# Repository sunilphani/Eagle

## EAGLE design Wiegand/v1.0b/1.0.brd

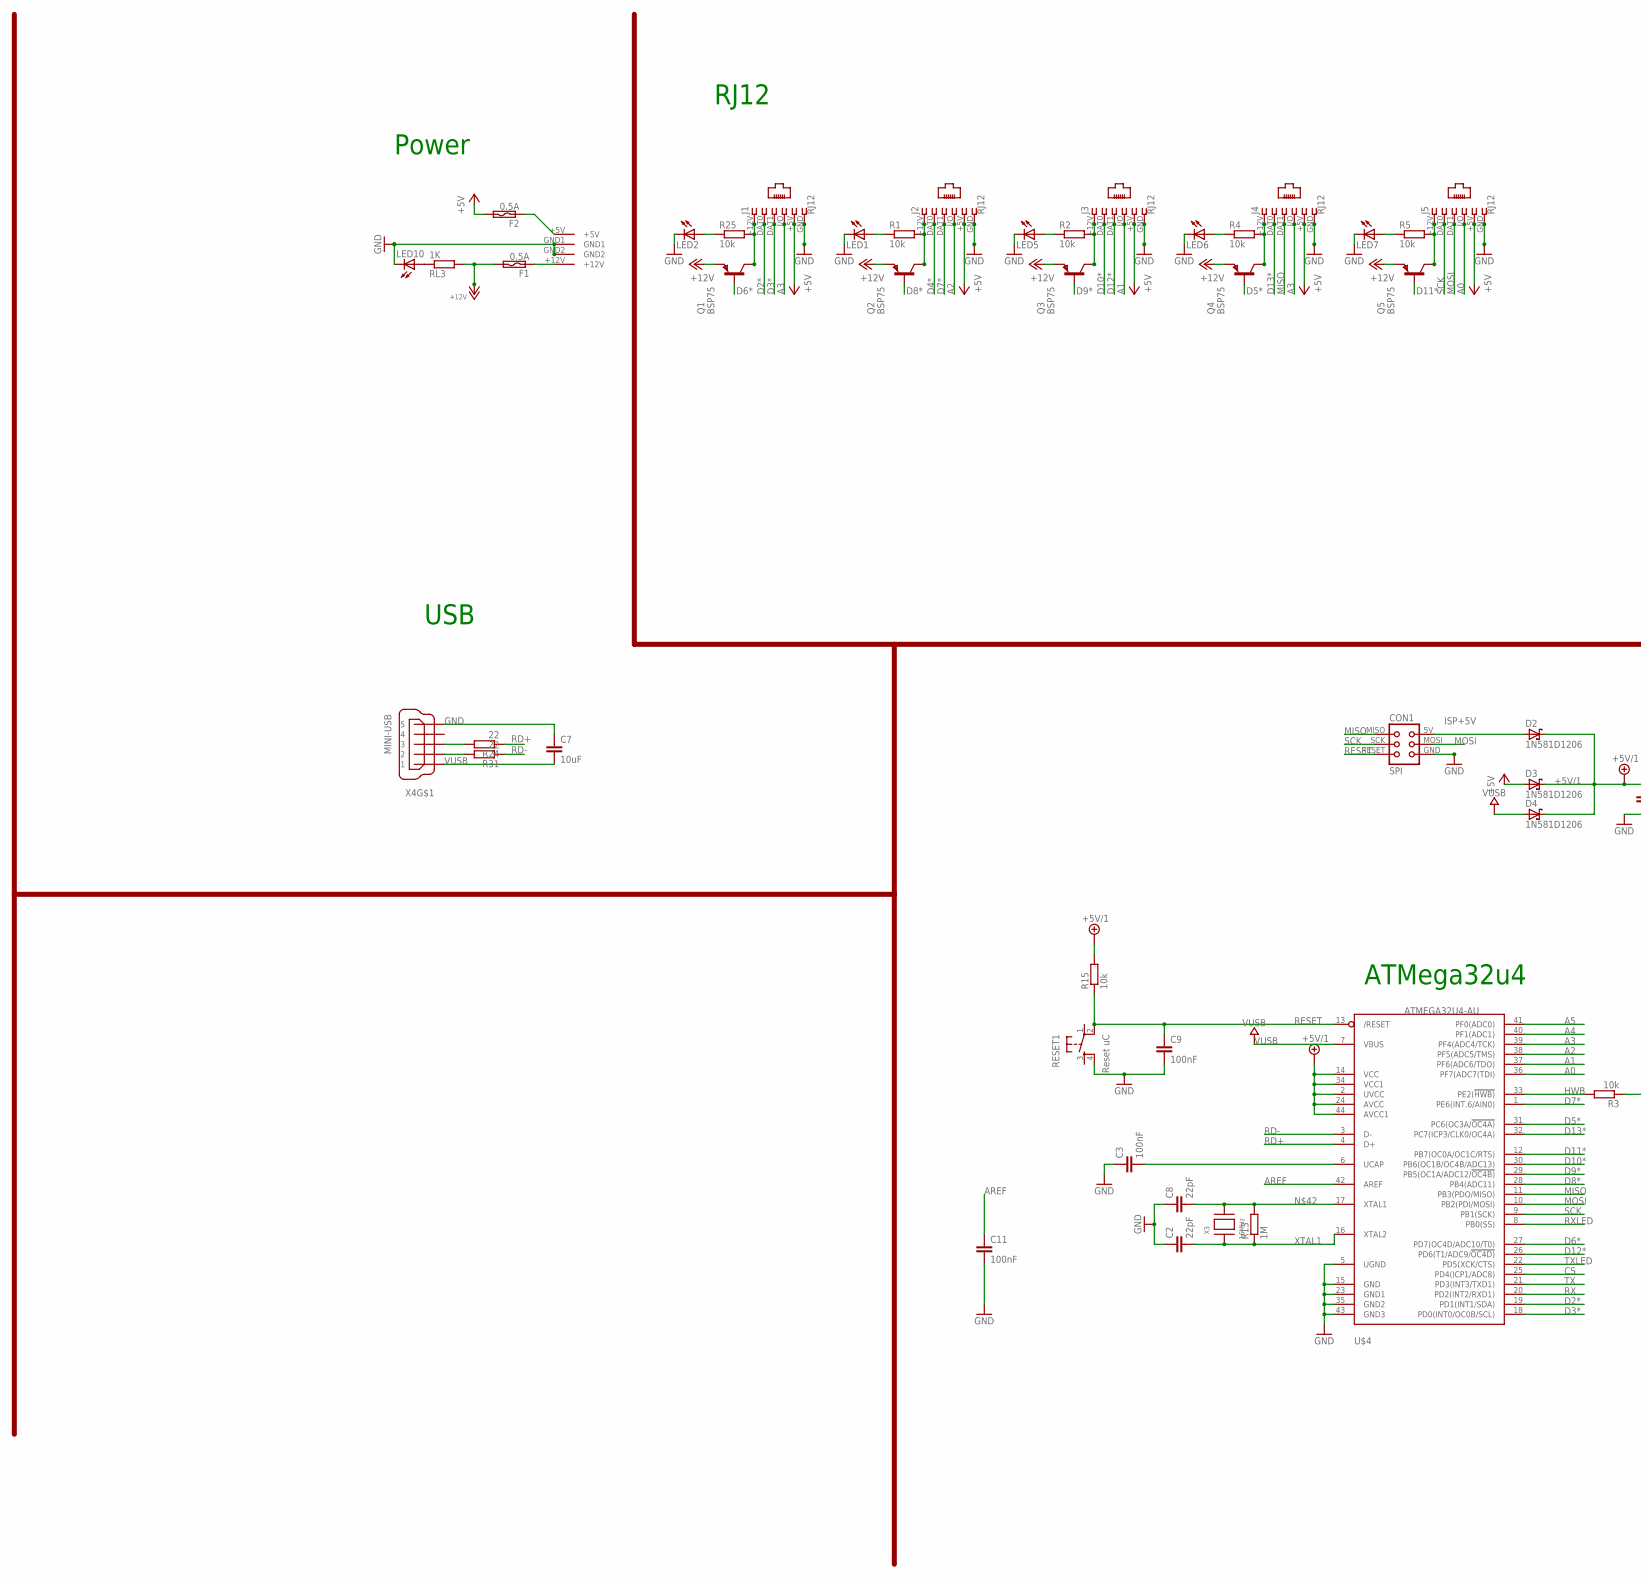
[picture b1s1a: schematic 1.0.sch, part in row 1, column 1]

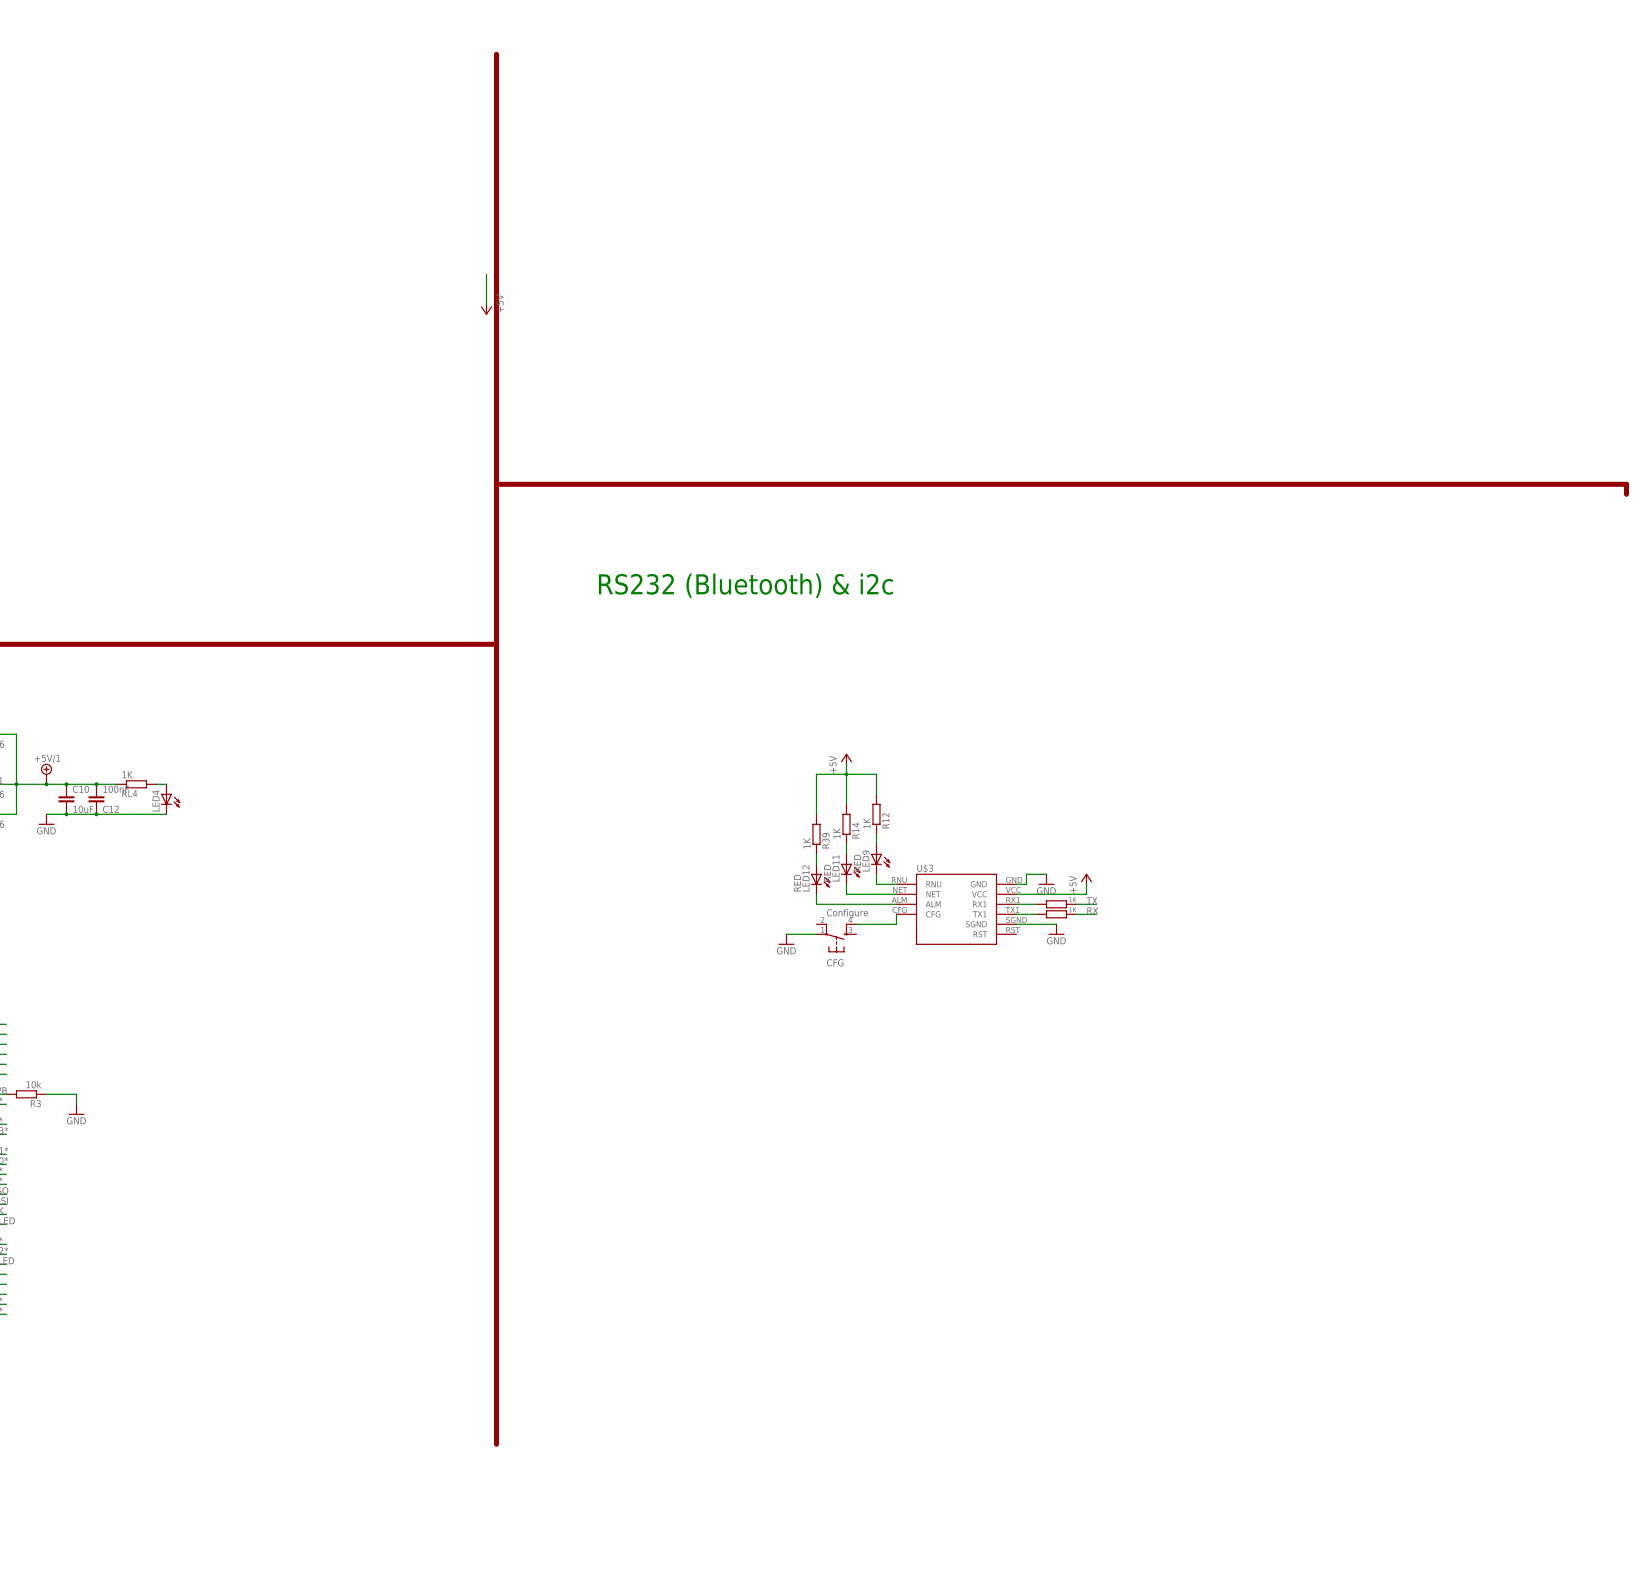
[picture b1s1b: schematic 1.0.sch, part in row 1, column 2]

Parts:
C2, C8: 22pF; C1206
C3, C9, C11, C12: 100nF; C1206
C7, C10: 10uF; C1206
CFG: Configure; TACTILE_SWITCH_SMD
CON1: SPI; TC2030-MCP
D2, D3, D4: 1N581D1206; LED-1206
F1, F2: 0.5A; C1812
J1, J2, J3, J4, J5: RJ12; RJ12-STRAIGHT-WIEGAND
LED1, LED2, LED5, LED6, LED7: Blue; LED3MM
LED4, LED10: RED; LED3MM
LED9, LED11, LED12: RED; CHIP-LED0805
Q1, Q2, Q3, Q4, Q5: BSP75; SOT223
R1, R2, R4, R5, R25: 10k; R0805
R3, R15: 10k; M0805
R8, R11, R12, R14, R39: 1K; R0805
R13: 1M; R1206
R24, R31: 22; M1206
RESET1: Reset uC; TACTILE_SWITCH_SMD
RL3, RL4: 1K; R0805
U$3: SZ05-ZIGBEE
U$4: ATMEGA32U4-AU; TQFP44
U$6: KPJX-4S-S
X3: 16MHz; NX6035
X4: MINI-USB; 32005-201

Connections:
+5V: D3.A, F2.2, J1.+5V (5), J2.+5V (5), J3.+5V (5), J4.+5V (5), J5.+5V (5), R12.2, R14.2, R39.2, U$3.VCC
+5V/1: C10.1, C12.2, D2.C, D3.C, D4.C, R15.2, RL4.1, U$4.2 (UVCC), U$4.14 (VCC), U$4.24 (AVCC), U$4.34 (VCC1), U$4.44 (AVCC1)
+12V: F1.2, Q1.3 (E), Q2.3 (E), Q3.3 (E), Q4.3 (E), Q5.3 (E), RL3.2
A0: J5.I/O (4), U$4.36 (PF7(ADC7(TDI))
A1: J3.I/O (4), U$4.37 (PF6(ADC6/TDO))
A2: J2.I/O (4), U$4.38 (PF5(ADC5/TMS))
A3: J1.I/O (4), J4.I/O (4), U$4.39 (PF4(ADC4/TCK))
A4: U$4.40 (PF1(ADC1))
A5: U$4.41 (PF0(ADC0))
AREF: C11.1, U$4.42 (AREF)
CS: U$4.25 (PD4(ICP1/ADC8))
D2*: J1.DAT0 (2), U$4.19 (PD1(INT1/SDA))
D3*: J1.DAT1 (3), U$4.18 (PD0(INT0/OC0B/SCL))
D4*: J2.DAT0 (2)
D5*: Q4.1 (B), U$4.31 (PC6(OC3A/!OC4A))
D6*: Q1.1 (B), U$4.27 (PD7(OC4D/ADC10/T0))
D7*: J2.DAT1 (3), U$4.1 (PE6(INT.6/AIN0))
D8*: Q2.1 (B), U$4.28 (PB4(ADC11))
D9*: Q3.1 (B), U$4.29 (PB5(OC1A/ADC12/!OC4B))
D10*: J3.DAT0 (2), U$4.30 (PB6(OC1B/OC4B/ADC13))
D11*: Q5.1 (B), U$4.12 (PB7(OC0A/OC1C/RTS))
D12*: J3.DAT1 (3), U$4.26 (PD6(T1/ADC9/!OC4D))
D13*: J4.DAT0 (2), U$4.32 (PC7(ICP3/CLK0/OC4A))
D+USB: R24.2, X4.3
D-USB: R31.2, X4.2
GND: C2.1, C3.1, C7.1, C8.1, C9.2, C10.2, C11.2, C12.1, CFG.1, CON1.GND, J1.GND (6), J2.GND (6), J3.GND (6), J4.GND (6), J5.GND (6), LED1.K (C), LED2.K (C), LED4.K (C), LED5.K (C), LED6.K (C), LED7.K (C), LED10.K (C), R3.1, RESET1.4, U$3.GND, U$3.SGND, U$4.5 (UGND), U$4.15 (GND), U$4.23 (GND1), U$4.35 (GND2), U$4.43 (GND3), U$6.GND1, U$6.GND2, X4.5
GND1: LED9.C, U$3.RNU
GND2: LED11.C, U$3.NET
GND3: LED12.C, U$3.ALM
HWB: R3.2, U$4.33 (PE2(!HWB))
ISP+5V: CON1.5V (VCC), D2.A
MISO: CON1.MISO, J4.DAT1 (3), U$4.11 (PB3(PDO/MISO))
MOSI: CON1.MOSI, J5.DAT1 (3), U$4.10 (PB2(PDI/MOSI))
unnamed: LED1.A, R1.1
unnamed: J2.+12V (1), Q2.2 (C), Q2.4 (C), R1.2
unnamed: LED5.A, R2.1
unnamed: J3.+12V (1), Q3.2 (C), Q3.4 (C), R2.2
unnamed: R11.2, U$3.RX1
unnamed: LED4.A, RL4.2
unnamed: C3.2, U$4.6 (UCAP)
unnamed: LED2.A, R25.1
unnamed: LED6.A, R4.1
unnamed: J4.+12V (1), Q4.2 (C), Q4.4 (C), R4.2
unnamed: J1.+12V (1), Q1.2 (C), Q1.4 (C), R25.2
unnamed: R8.2, U$3.TX1
unnamed: LED9.A, R12.1
unnamed: LED11.A, R14.1
unnamed: LED12.A, R39.1
unnamed: LED7.A, R5.1
unnamed: J5.+12V (1), Q5.2 (C), Q5.4 (C), R5.2
unnamed: CFG.4, U$3.CFG
unnamed: F2.1, U$6.+5V
unnamed: F1.1, U$6.+12V
unnamed: C8.2, R13.2, U$4.17 (XTAL1), X3.P$2
unnamed: LED10.A, RL3.1
RD+: R24.1, U$4.4 (D+)
RD-: R31.1, U$4.3 (D-)
RESET: C9.1, CON1.RESET, R15.1, RESET1.2, U$4.13 (/RESET)
RX: R8.1, U$4.20 (PD2(INT2/RXD1))
RXLED: U$4.8 (PB0(SS))
SCK: CON1.SCK, J5.DAT0 (2), U$4.9 (PB1(SCK))
TX: R11.1, U$4.21 (PD3(INT3/TXD1))
TXLED: U$4.22 (PD5(XCK/CTS))
VUSB: C7.2, D4.A, U$4.7 (VBUS), X4.1
XTAL1: C2.2, R13.1, U$4.16 (XTAL2), X3.P$1

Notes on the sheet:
RJ12
ATMega32u4
USB
Power
RS232 (Bluetooth) & i2c

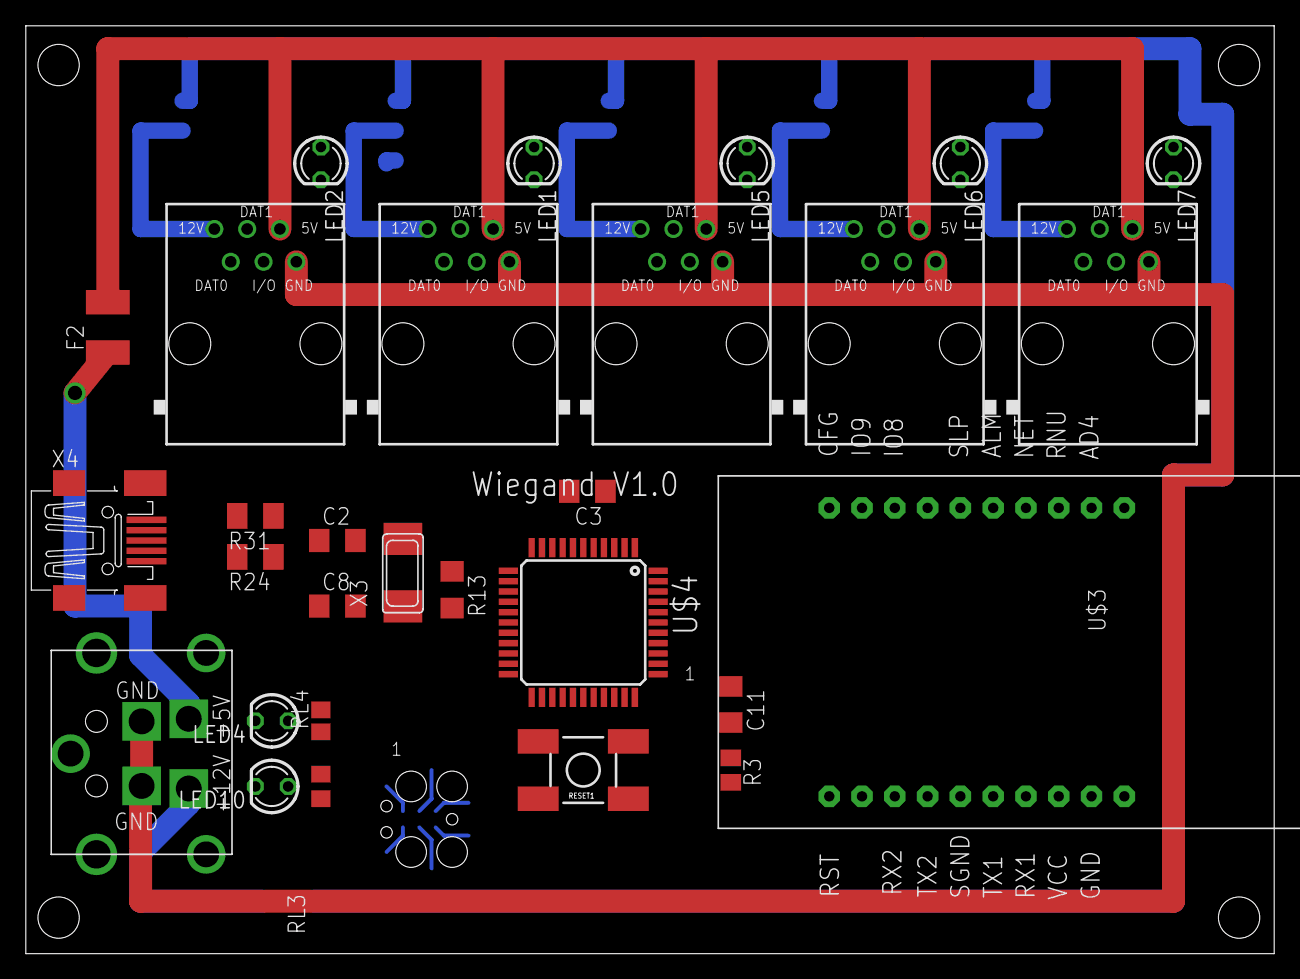
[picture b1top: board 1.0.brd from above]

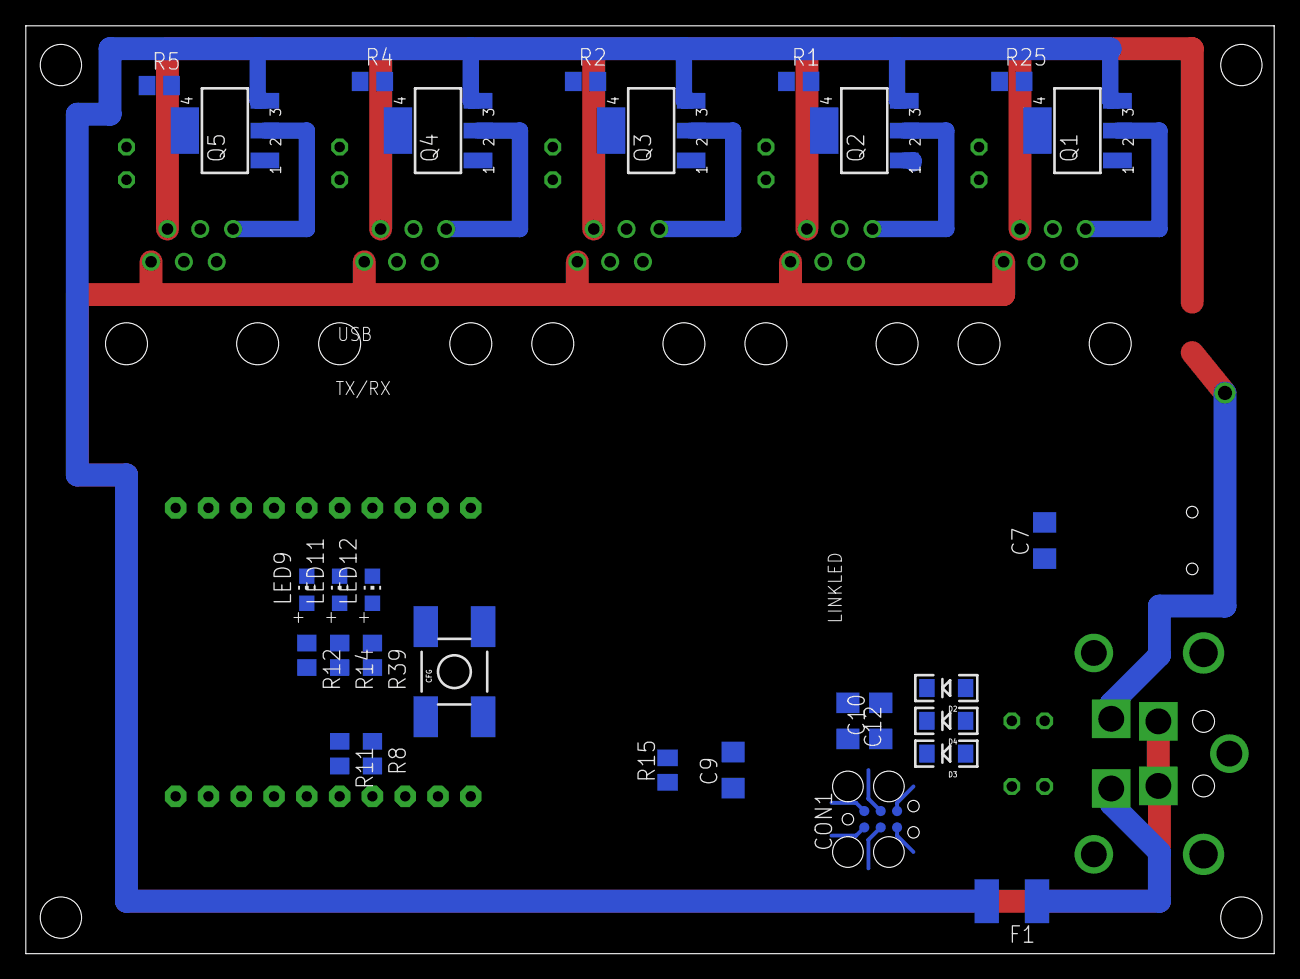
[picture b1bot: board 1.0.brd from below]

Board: 2 copper layers, 96.7 x 71.9 mm, 58 parts (29 on the bottom side), 59 nets.

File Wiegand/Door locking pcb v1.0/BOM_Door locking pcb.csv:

"Qty";"Value";"Device";"Package";"Parts";"Description";"";
"4";"100nF";"C-EUC1206";"C1206";"C3, C9, C11, C12";"CAPACITOR, European symbol";"";
"1";"10K";"R-EU_R0805";"R0805";"RL2";"RESISTOR, European symbol";"";
"2";"10k";"R-EU_M0805";"M0805";"R3, R15";"RESISTOR, European symbol";"";
"2";"10uF";"C-EUC1206";"C1206";"C7, C10";"CAPACITOR, European symbol";"";
"1";"16MHz";"XTALNX6035";"NX6035";"X3";"Low cost SMT crystals, no capacitors included";"";
"8";"1K";"R-EU_R0805";"R0805";"R8, R11, R12, R14, R39, RL3, RL4, RL5";"RESISTOR, European symbol";"";
"1";"1M";"R-EU_R1206";"R1206";"R13";"RESISTOR, European symbol";"";
"3";"1N581D1206";"1N581D1206";"LED-1206";"D2, D3, D4";"1.0A SCHOTTKY BARRIER RECTIFIER";"";
"2";"22";"R-EU_M1206";"M1206";"R24, R31";"RESISTOR, European symbol";"";
"2";"22--02";"22--02";"2-PIN-5.08S";"J1, J7";"CONNECTOR";"";
"2";"22pF";"C-EUC1206";"C1206";"C2, C8";"CAPACITOR, European symbol";"";
"1";"ATMEGA32U4-AU";"ATMEGA32U4-AU";"TQFP44";"U$4";"http://www.ladyada.net/library/eagle";"";
"2";"BSP75";"BSP613P";"PG-SOT-223";"Q1, Q3";"SIPMOS (R) Small-Signal-Transistor P-Channel (2 Drain)";"";
"1";"Configure";"TAC_SWITCHSMD";"TACTILE_SWITCH_SMD";"CFG";"Momentary Switch";"";
"1";"GREEN";"LEDCHIPLED_1206";"CHIPLED_1206";"LED1";"LED";"";
"1";"KPJX-4S-S";"KPJX-4S-S";"KPJX-4S-S";"U$6";"";"";
"1";"MINI-USB";"MINI-USB-SCHIELD-32005-201";"32005-201";"X4";"MINI USB-B Conector";"";
"5";"RED";"LEDCHIPLED_1206";"CHIPLED_1206";"LED4, LED9, LED10, LED11, LED12";"LED";"";
"1";"Reset uC";"TAC_SWITCHSMD";"TACTILE_SWITCH_SMD";"RESET1";"Momentary Switch";"";
"1";"SPI";"TINYISPT";"TC2030-MCP-NL";"CON1";"CONNECTOR";"";
"1";"SZ05-ZIGBEE";"SZ05-ZIGBEE";"SZ05-ZIGBEE";"U$3";"";"";
"6";"TERMINALSUPERFICIAL";"TERMINALSUPERFICIAL";"ELPUTAS";"PIN1, PIN2, PIN3, PIN4, PIN5, PIN6";"";"";

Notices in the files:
parts and their libraries:
lpatiny: ©2009 ROFA.cz - modified and updated by Robert Darlington ‹rdarlington@gmail.com›
SparkFun: Licensing: CC v3.0 Share-Alike You are welcome to use this library for commercial purposes.
